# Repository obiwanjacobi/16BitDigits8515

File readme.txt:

This project is a four-digit 7-segments display that decodes 16-bit of data into a hexadecimal notation.

Uses an ATmega8515 to read the 16 input bits and multiplex a common cathode 4-digit 7-segment display.

Folders:
--------
KiCad	                  - contains the schematic and a rough board layout.
FourSevenSegment8515      - contains the Arduino sketch for the ATmega8515 with instructions how to program.

Discussed on EEVBlog Forum: https://www.eevblog.com/forum/projects/16-bit-to-4-digit-7-segment-decoder

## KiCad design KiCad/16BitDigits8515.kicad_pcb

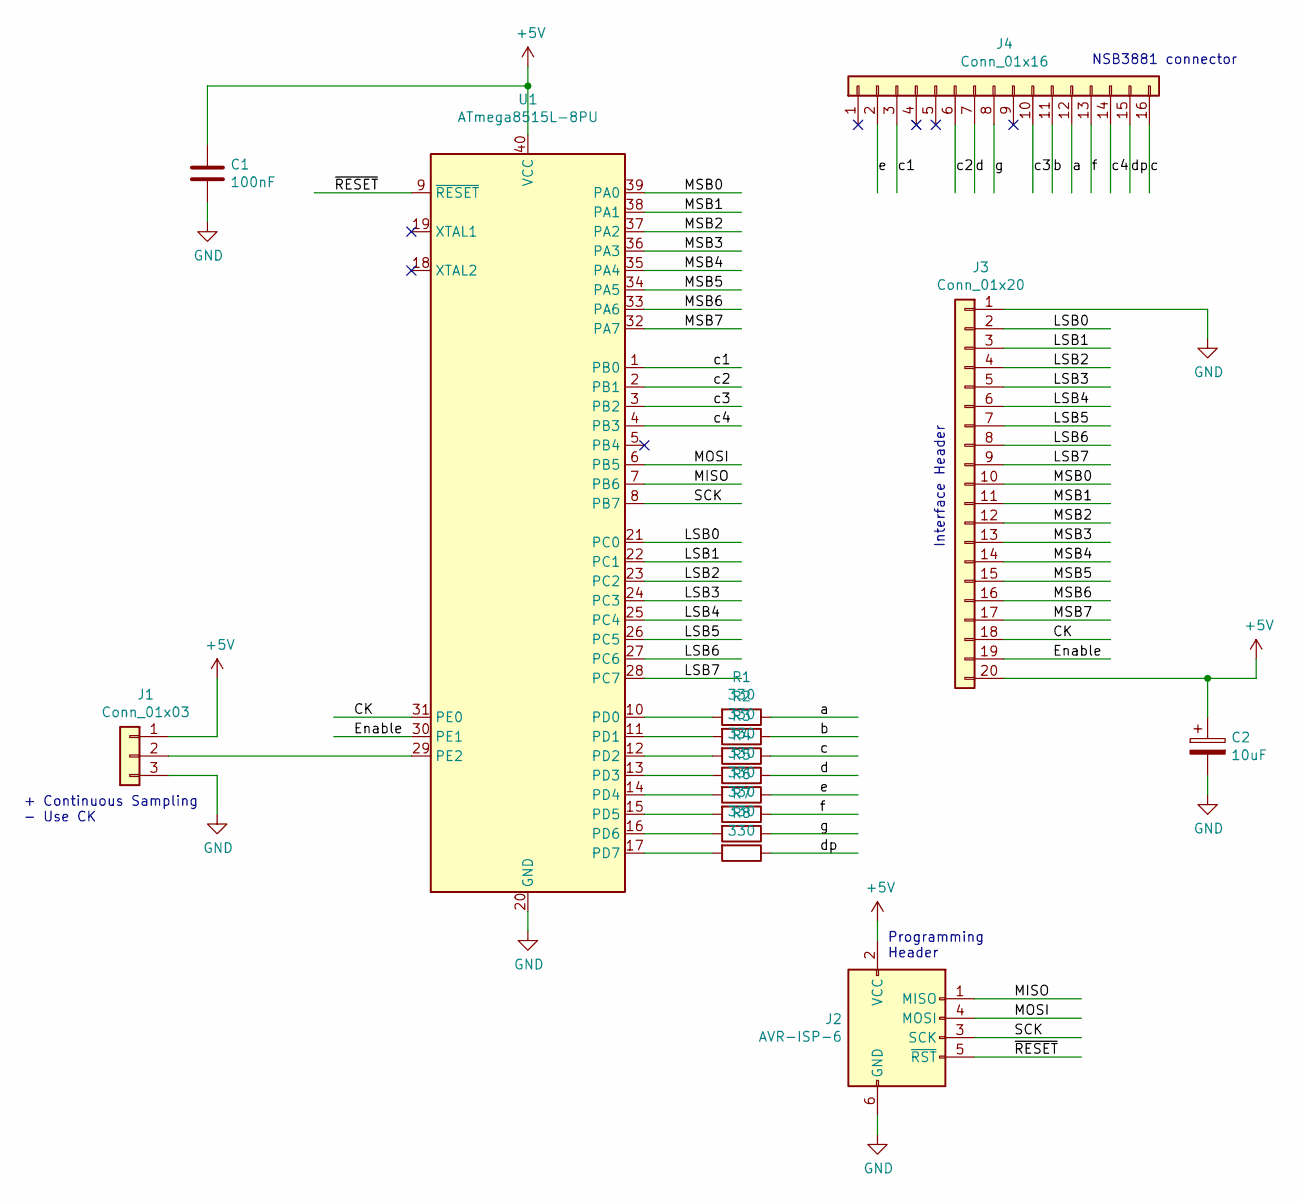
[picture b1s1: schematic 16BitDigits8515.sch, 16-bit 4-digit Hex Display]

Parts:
C1: 100nF; C_Rect_L9.0mm_W2.5mm_P7.50mm_MKT
C2: 10uF; CP_Radial_D5.0mm_P2.50mm
J1: Conn_01x03; PinHeader_1x03_P2.54mm_Vertical
J2: AVR-ISP-6; PinHeader_2x03_P2.54mm_Vertical
J3: Conn_01x20; PinHeader_1x20_P2.54mm_Vertical
J4: Conn_01x16; PinHeader_1x16_P2.54mm_Vertical
R1, R2, R3, R4, R5, R6, R7, R8: 330; R_Axial_DIN0207_L6.3mm_D2.5mm_P10.16mm_Horizontal
U1: ATmega8515L-8PU; DIP-40_W15.24mm

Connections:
+5V: C1.1, C2.1, J1.1, J2.2 (VCC), J3.20, U1.40 (VCC)
/CK: J3.18, U1.31 (PE0)
/Enable: J3.19, U1.30 (PE1)
/LSB0: J3.2, U1.21 (PC0)
/LSB1: J3.3, U1.22 (PC1)
/LSB2: J3.4, U1.23 (PC2)
/LSB3: J3.5, U1.24 (PC3)
/LSB4: J3.6, U1.25 (PC4)
/LSB5: J3.7, U1.26 (PC5)
/LSB6: J3.8, U1.27 (PC6)
/LSB7: J3.9, U1.28 (PC7)
/MISO: J2.1 (MISO), U1.7 (PB6)
/MOSI: J2.4 (MOSI), U1.6 (PB5)
/MSB0: J3.10, U1.39 (PA0)
/MSB1: J3.11, U1.38 (PA1)
/MSB2: J3.12, U1.37 (PA2)
/MSB3: J3.13, U1.36 (PA3)
/MSB4: J3.14, U1.35 (PA4)
/MSB5: J3.15, U1.34 (PA5)
/MSB6: J3.16, U1.33 (PA6)
/MSB7: J3.17, U1.32 (PA7)
/SCK: J2.3 (SCK), U1.8 (PB7)
/a: J4.12, R1.1
/b: J4.11, R2.1
/c: J4.16, R3.1
/c1: J4.3, U1.1 (PB0)
/c2: J4.6, U1.2 (PB1)
/c3: J4.10, U1.3 (PB2)
/c4: J4.14, U1.4 (PB3)
/d: J4.7, R4.1
/dp: J4.15, R8.1
/e: J4.2, R5.1
/f: J4.13, R6.1
/g: J4.8, R7.1
/~RESET: J2.5 (~RST), U1.9 (~RESET)
GND: C1.2, C2.2, J1.3, J2.6 (GND), J3.1, U1.20 (GND)
unnamed: J1.2, U1.29 (PE2)
unnamed: R1.2, U1.10 (PD0)
unnamed: R2.2, U1.11 (PD1)
unnamed: R3.2, U1.12 (PD2)
unnamed: R4.2, U1.13 (PD3)
unnamed: R5.2, U1.14 (PD4)
unnamed: R6.2, U1.15 (PD5)
unnamed: R7.2, U1.16 (PD6)
unnamed: R8.2, U1.17 (PD7)

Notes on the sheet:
NSB3881 connector
+ Continuous Sampling - Use CK
Interface Header
Programming Header

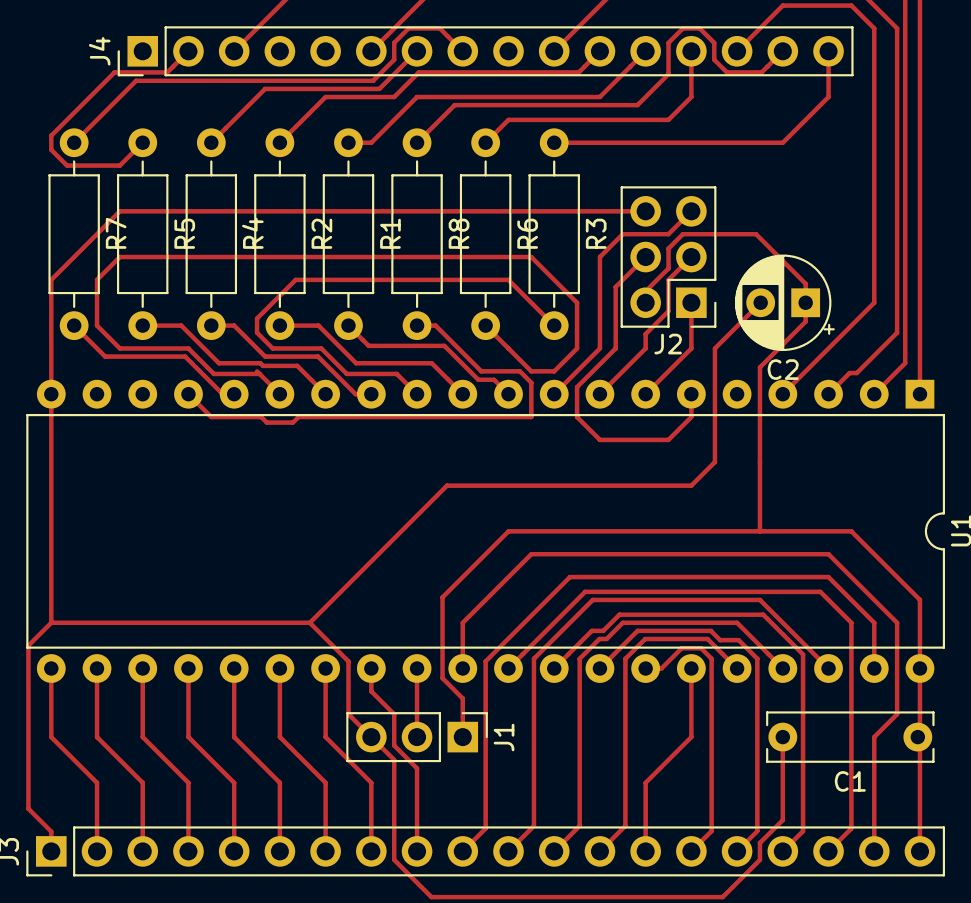
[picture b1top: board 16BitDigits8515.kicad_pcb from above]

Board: 2 copper layers, 15 parts (0 on the bottom side), 45 nets.
